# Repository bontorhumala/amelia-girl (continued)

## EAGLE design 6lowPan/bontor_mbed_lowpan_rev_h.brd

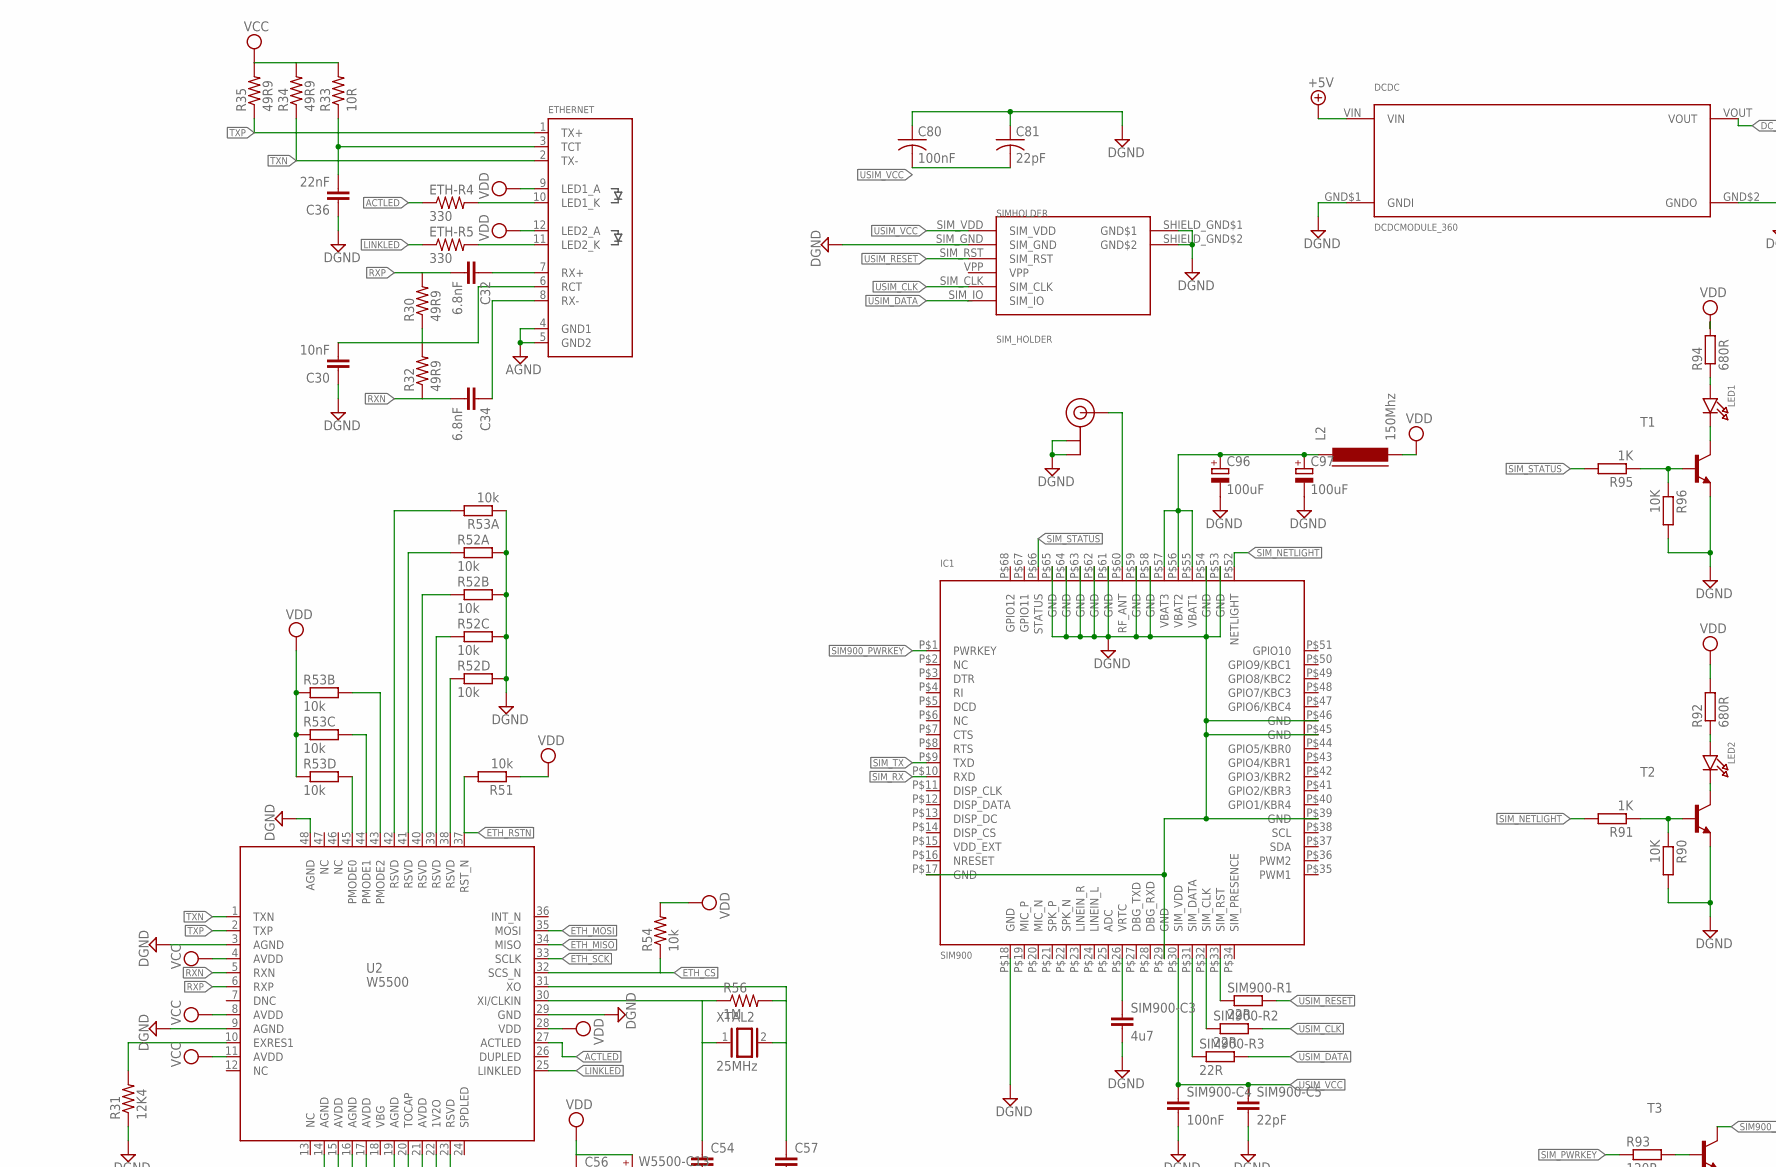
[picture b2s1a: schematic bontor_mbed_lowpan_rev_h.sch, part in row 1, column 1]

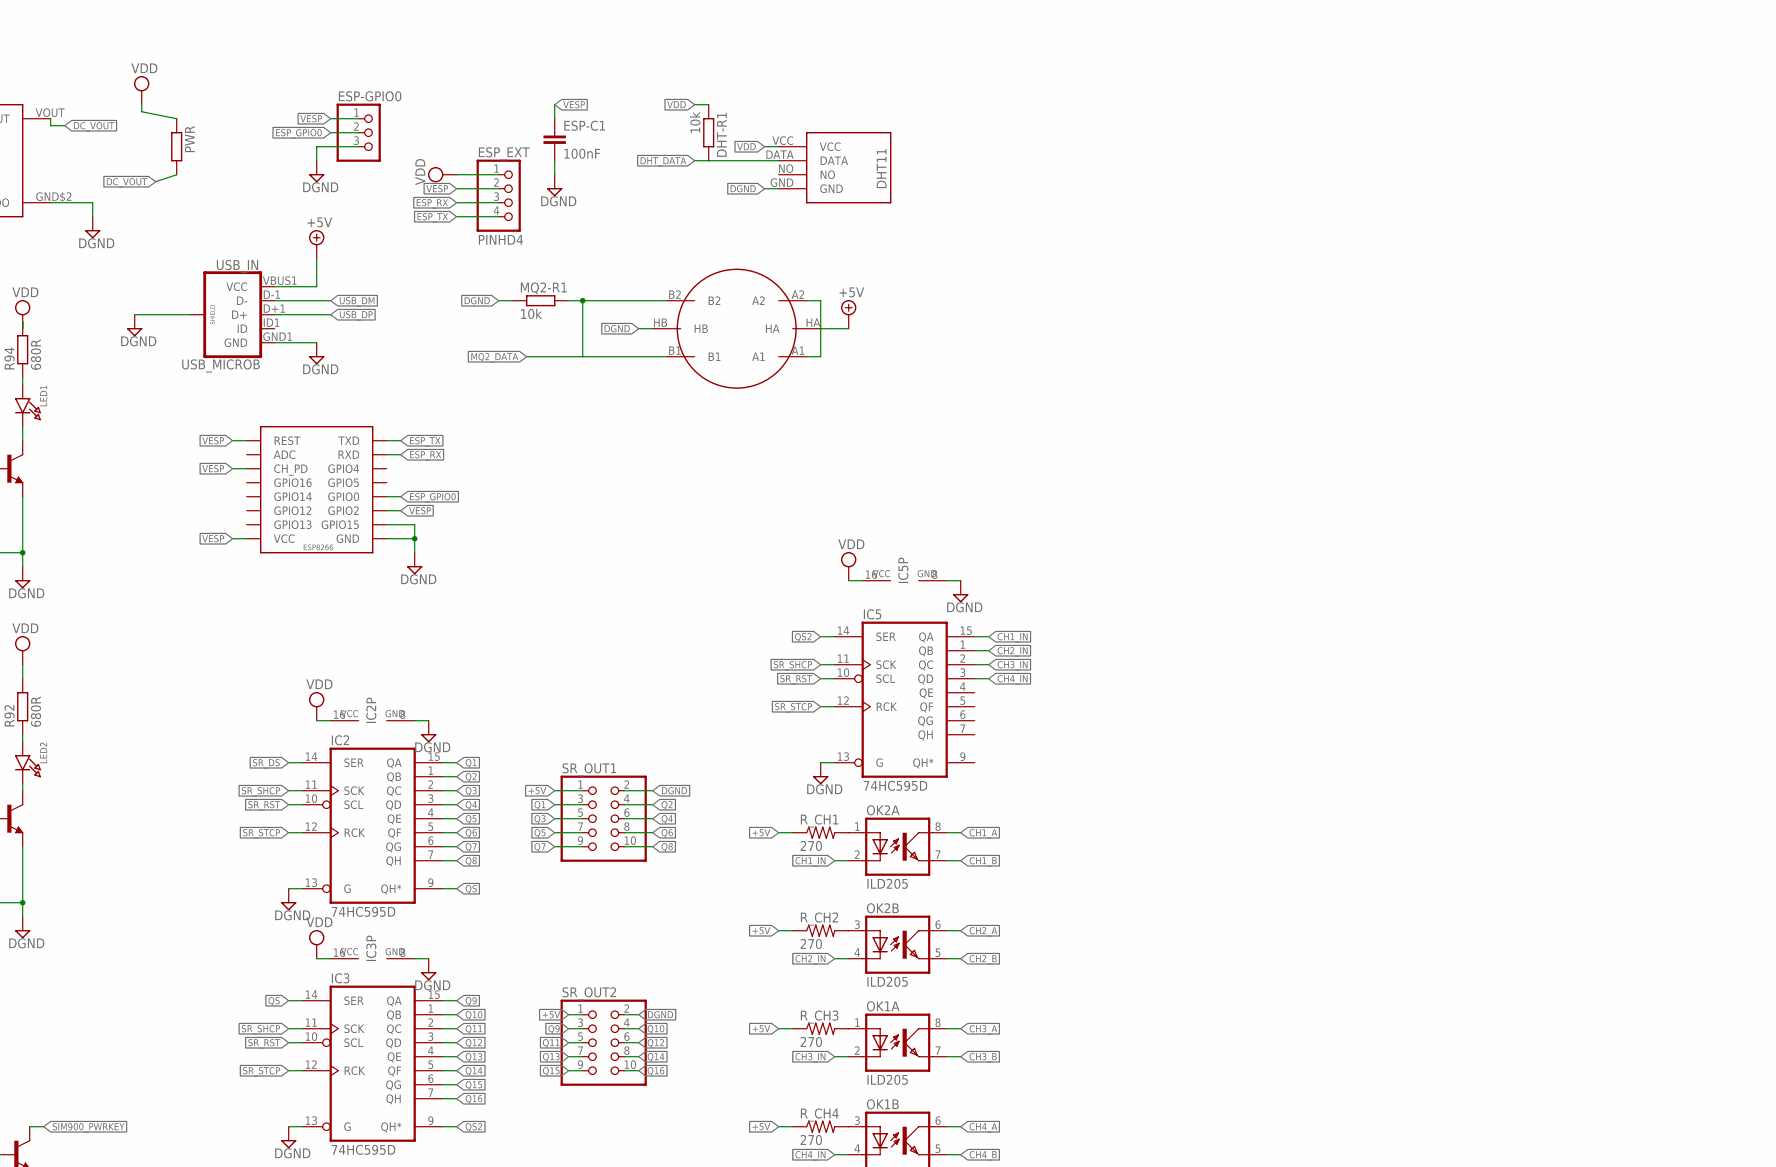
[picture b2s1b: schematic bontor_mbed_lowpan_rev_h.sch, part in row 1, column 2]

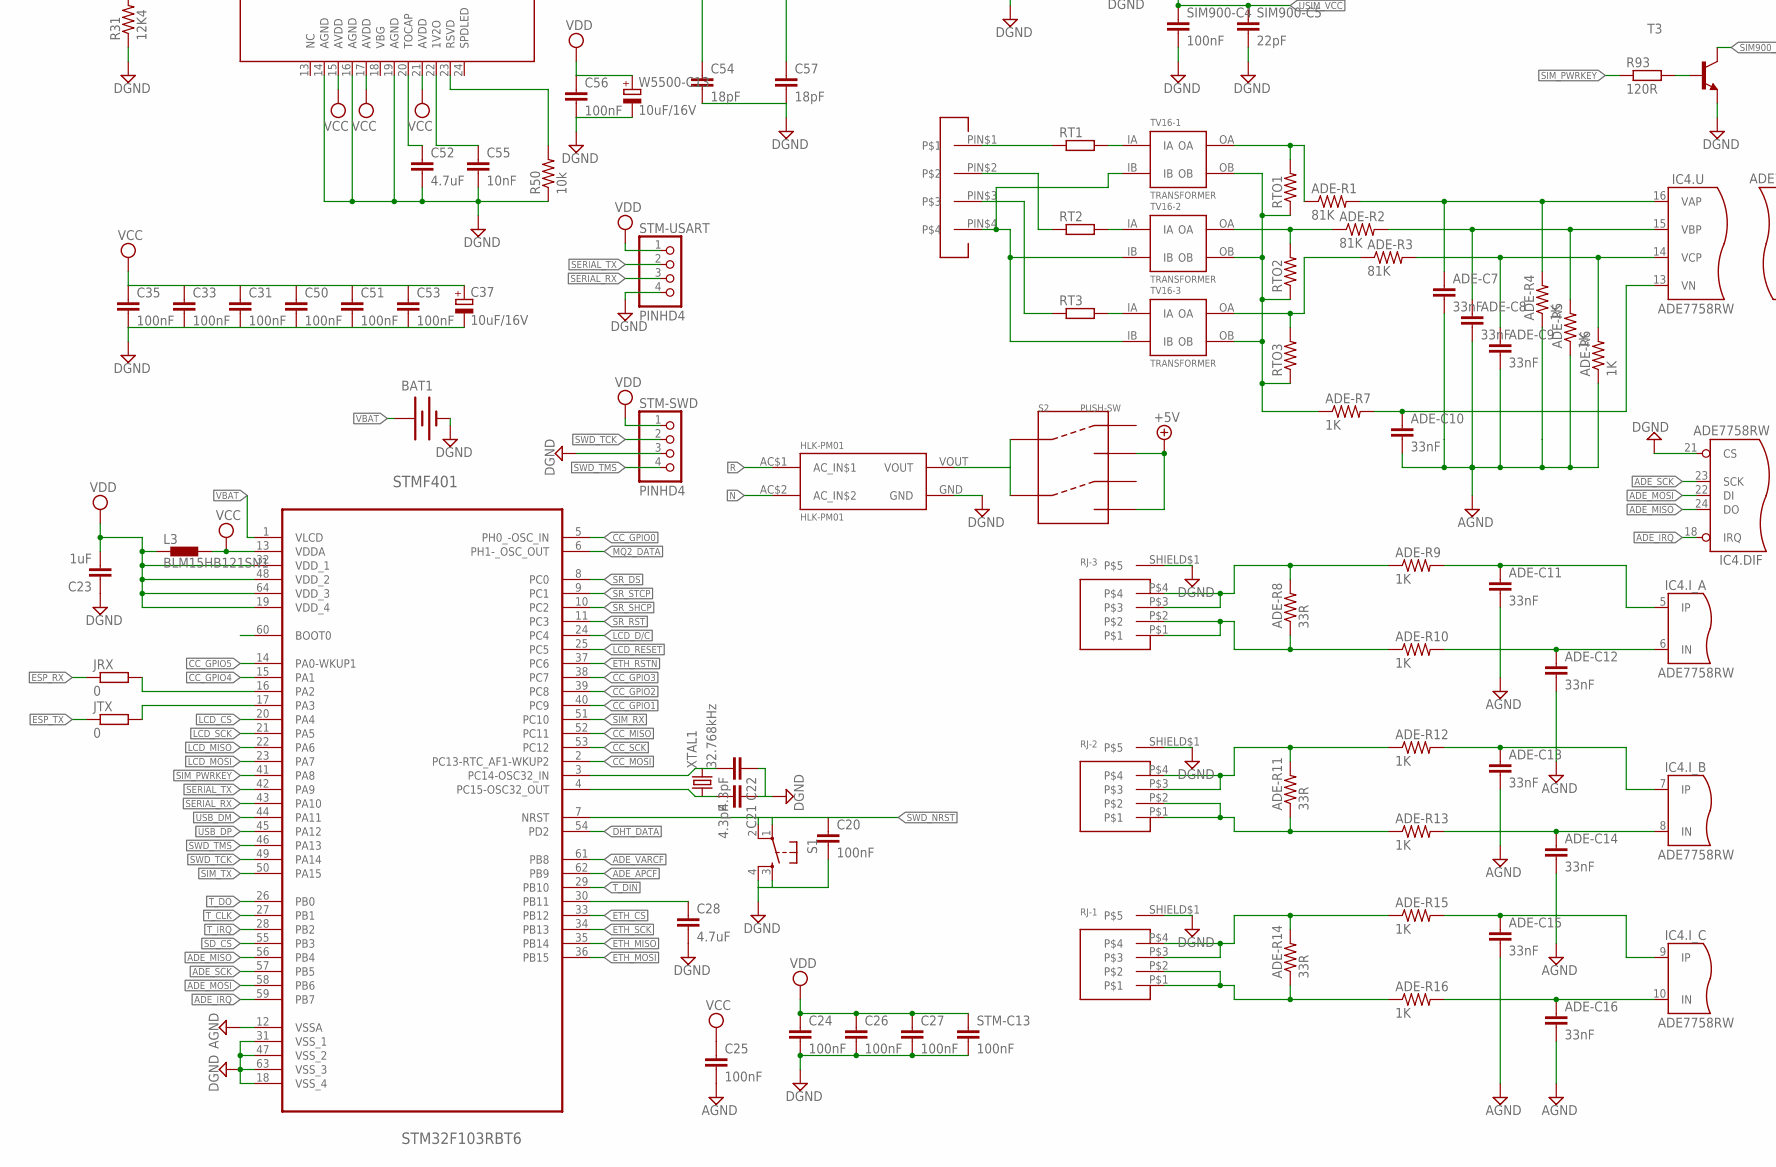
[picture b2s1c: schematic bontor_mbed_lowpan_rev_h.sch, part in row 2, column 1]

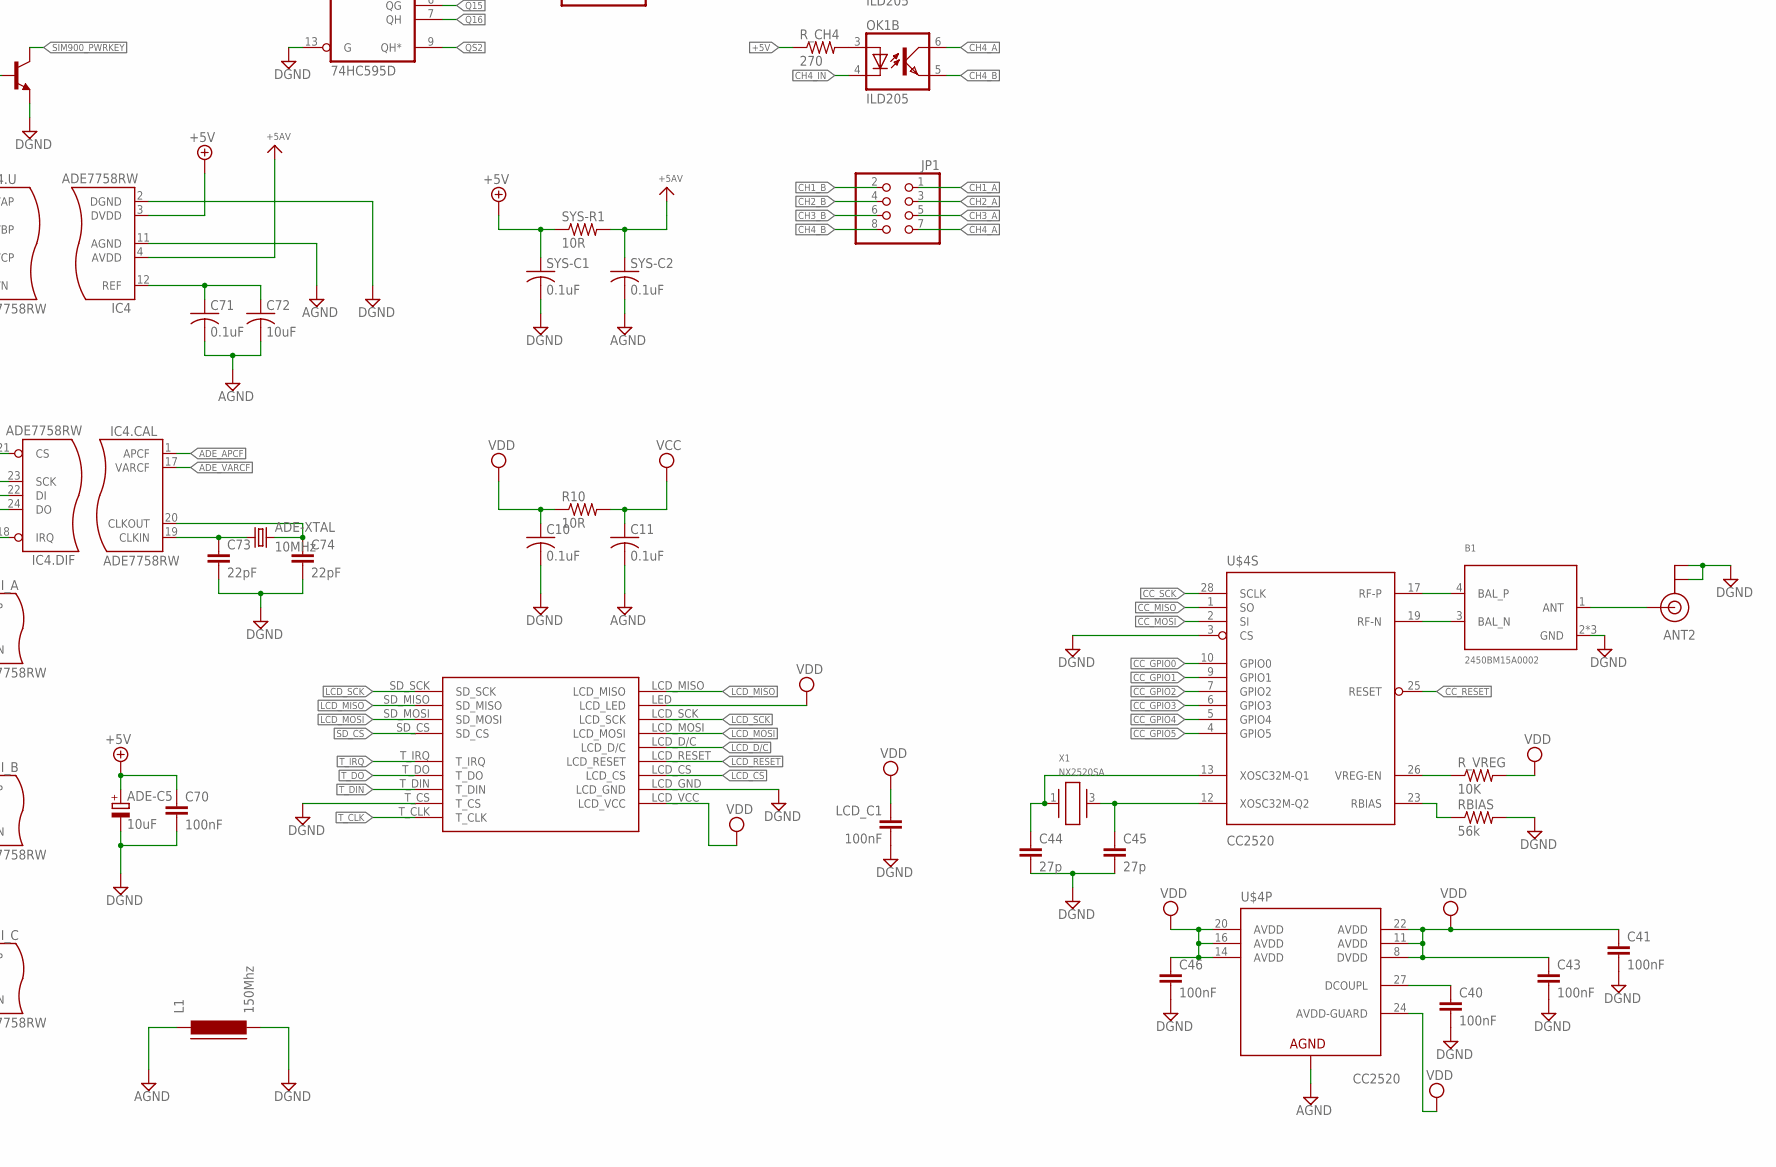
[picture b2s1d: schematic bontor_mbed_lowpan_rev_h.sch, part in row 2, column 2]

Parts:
ADE-C5: 10uF; 153CLV-0605
ADE-C7, ADE-C8, ADE-C9, ADE-C10: 33nF; 0603-CAP
ADE-C11, ADE-C12, ADE-C13, ADE-C14, ADE-C15, ADE-C16: 33nF; 0402-CAP
ADE-R1, ADE-R2, ADE-R3: 81K; 0603-RES
ADE-R4, ADE-R5, ADE-R6, ADE-R7: 1K; 0603-RES
ADE-R8, ADE-R11, ADE-R14: 33R; 0402-RES
ADE-R9, ADE-R10, ADE-R12, ADE-R13, ADE-R15, ADE-R16: 1K; 0402-RES
ADE-XTAL: 10MHz; HC49US
ANT1, ANT2: U.FL
B1: 2450BM15A0002; 2450BM
BAT1: BATTERY12MM; BATTCON_12MM
C10, C11, C71: 0.1uF; C0603
C20, C24, C25, C26, C31, C33, C35, C50, C51, C53, C56, C70: 100nF; C0603
C21, C22: 4.3pF; C0603
C23: 1uF; C0603
C27, C40, C41, C43, C46: 100nF; C0402
C28, C52: 4.7uF; C0603
C30, C55: 10nF; C0603
C32, C34: 6.8nF; C0603
C36: 22nF; C0603
C37: 10uF/16V; 153CLV-0605
C44, C45: 27p; C0201
C54, C57: 18pF; C0603
C72: 10uF; C0805K
C73, C74: 22pF; C0603
C80: 100nF; C0603K
C81: 22pF; C0603K
C96, C97: 100uF; 153CLV-0605
DCDC: DCDCMODULE_360; DCDCMODULE-360
DHT-R1: 10k; R0603
ESP: ESP; WI12
ESP-C1: 100nF; C0603
ESP-GPIO0: PINHD-1X3; 1X03
ESP_EXT: PINHD4
ETH-R4, ETH-R5: 330; R0603
ETHERNET: RJ45J0026D21BNL; RJ45_PULSEJACK
HLK-PM01: HLK-PM01
IC1: SIM900; SIM900_SMT
IC2, IC3, IC5: 74HC595D; SO16
IC4: ADE7758RW; SOIC24
JP1: PINHD-2X4; 2X04
JRX: 0; R0603
JTX: 0; R0603
L1, L2: 150Mhz; FB805
L3: BLM15HB121SN1; 0402
LCD14: LCD_2.4; LCD_TOUCH_2-4
LCD_C1: 100nF; C0603
LED1, LED2: LED0805_NOOUTLINE; CHIPLED_0805_NOOUTLINE
MQ2-R1: 10k; R0603
OK1, OK2: ILD205; SOIC08
PWR: R-EU_R0805; R0805
R10: 10R; 0603-RES
R30, R32, R34, R35: 49R9; R0603
R31: 12K4; R0805
R33: 10R; R0603
R50, R51, R54: 10k; R0603
R52, R53: 10k; RN8P-4R-CRA06S
R56: 1M; R0603
R90, R96: 10K; R0603
R91, R95: 1K; R0603
R92, R94: 680R; R0603
R93: 120R; R0603
RBIAS: 56k; 0402-RES
RJ-1, RJ-2, RJ-3: RJ11-4P-V
RT1, RT2, RT3: R-EU_0309/V; 0309V
RTO1, RTO2, RTO3: R-US_0309_12; 0309_12
R_CH1, R_CH2, R_CH3, R_CH4: 270; 0603-RES
R_VREG: 10K; 0402-RES
S1: TAC_SWITCHPTH; TACTILE-PTH
S2: PUSH-SW; SWITCH-6PIN-LOCK-2.54MM
SENSOR-MQ2: METHANE_SENSOR; MQ-3
SIM900-C3: 4u7; C0603
SIM900-C4: 100nF; C0603
SIM900-C5: 22pF; C0603
SIM900-R1, SIM900-R2, SIM900-R3: 22R; R0603
SIMHOLDER: SIM_HOLDER; SIMHOLDER-PUSHPUSH
SR_OUT1, SR_OUT2: PINHD-2X5; 2X05
STM-C13: 100nF; C0603
STM-SWD: PINHD4
STM-USART: PINHD4
STMF401: STM32F103RBT6; QFP50P1200X1200X160-64N
SYS-C1, SYS-C2: 0.1uF; C0603
SYS-R1: 10R; 0603-RES
T1, T2, T3: MMBT2222ALT1-NPN-SOT23-BEC; SOT23-BEC
TERM_BLOCK: TERMINAL_BLOCK_TW; TERMINAL-TWO-WAY
TV16-1, TV16-2, TV16-3: TRANSFORMER; TV16
U2: W5500
U$4: CC2520; QFN50P500X500X100-29N
U$17: DHT11
USB_IN: USB_MICROB; USB-B-MICRO-SMD_V03
W5500-C13: 10uF/16V; 153CLV-0605
X1: NX2520SA
XTAL1: 32.768kHz; TC26H
XTAL2: 25MHz; QS

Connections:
+5V: ADE-C5.+, C70.1, DCDC.VIN, IC4.3 (DVDD), R_CH1.1, R_CH2.1, R_CH3.1, R_CH4.1, S2.P$3, S2.P$6, SENSOR-MQ2.A1, SENSOR-MQ2.A2, SENSOR-MQ2.HA, SR_OUT1.1, SR_OUT2.1, SYS-C1.1, SYS-R1.1, USB_IN.VBUS1 (VCC)
ACTLED: ETH-R4.1, U2.27 (ACTLED)
ADE_APCF: IC4.1 (APCF), STMF401.62 (PB9)
ADE_IRQ: IC4.18 (IRQ), STMF401.59 (PB7)
ADE_MISO: IC4.24 (DO), STMF401.56 (PB4)
ADE_MOSI: IC4.22 (DI), STMF401.58 (PB6)
ADE_SCK: IC4.23 (SCK), STMF401.57 (PB5)
ADE_VARCF: IC4.17 (VARCF), STMF401.61 (PB8)
AGND: ADE-C7.2, ADE-C8.2, ADE-C9.2, ADE-C10.2, ADE-C11.2, ADE-C12.2, ADE-C13.2, ADE-C14.2, ADE-C15.2, ADE-C16.2, ADE-R4.1, ADE-R5.1, ADE-R6.1, C11.2, C25.2, C71.2, C72.2, ETHERNET.4 (GND1), ETHERNET.5 (GND2), IC4.11 (AGND), L1.1, STMF401.12 (VSSA), SYS-C2.2, U$4.29 (AGND)
AVDD: IC4.4 (AVDD), SYS-C2.1, SYS-R1.2
CC_GPIO0: STMF401.5 (PH0_-OSC_IN), U$4.10 (GPIO0)
CC_GPIO1: STMF401.40 (PC9), U$4.9 (GPIO1)
CC_GPIO2: STMF401.39 (PC8), U$4.7 (GPIO2)
CC_GPIO3: STMF401.38 (PC7), U$4.6 (GPIO3)
CC_GPIO4: STMF401.15 (PA1), U$4.5 (GPIO4)
CC_GPIO5: STMF401.14 (PA0-WKUP1), U$4.4 (GPIO5)
CC_MISO: STMF401.52 (PC11), U$4.1 (SO)
CC_MOSI: STMF401.2 (PC13-RTC_AF1-WKUP2), U$4.2 (SI)
CC_RESET: U$4.25 (RESET)
CC_SCK: STMF401.53 (PC12), U$4.28 (SCLK)
CH1_A: JP1.1, OK2.8 (COL)
CH1_B: JP1.2, OK2.7 (EMIT)
CH1_IN: IC5.15 (QA), OK2.2 (C)
CH2_A: JP1.3, OK2.6 (COL)
CH2_B: JP1.4, OK2.5 (EMIT)
CH2_IN: IC5.1 (QB), OK2.4 (C)
CH3_A: JP1.5, OK1.8 (COL)
CH3_B: JP1.6, OK1.7 (EMIT)
CH3_IN: IC5.2 (QC), OK1.2 (C)
CH4_A: JP1.7, OK1.6 (COL)
CH4_B: JP1.8, OK1.5 (EMIT)
CH4_IN: IC5.3 (QD), OK1.4 (C)
DC_VOUT: DCDC.VOUT, PWR.2
DGND: ADE-C5.-, ANT1.P$1 (GND), ANT1.P$2 (GND), ANT2.P$1 (GND), ANT2.P$2 (GND), B1.2 (GND), B1.5 (GND), B1.6 (GND), BAT1.GND (-), C10.2, C20.2, C21.1, C22.1, C23.1, C24.2, C26.2, C27.2, C28.2, C30.1, C31.2, C33.2, C35.2, C36.1, C37.-, C40.2, C41.2, C43.2, C44.2, C45.2, C46.2, C50.2, C51.2, C52.2, C53.2, C54.2, C55.2, C56.2, C57.2, C70.2, C73.2, C74.2, C80.1, C81.1, C96.-, C97.-, DCDC.GND$1 (GNDI), DCDC.GND$2 (GNDO), ESP.GND, ESP.GPIO15, ESP-C1.2, ESP-GPIO0.3, HLK-PM01.GND, IC1.P$17 (GND), IC1.P$18 (GND), IC1.P$29 (GND), IC1.P$39 (GND), IC1.P$45 (GND), IC1.P$46 (GND), IC1.P$53 (GND), IC1.P$54 (GND), IC1.P$58 (GND), IC1.P$59 (GND), IC1.P$61 (GND), IC1.P$62 (GND), IC1.P$63 (GND), IC1.P$64 (GND), IC1.P$65 (GND), IC2.8 (GND), IC2.13 (G), IC3.8 (GND), IC3.13 (G), IC4.2 (DGND), IC4.21 (CS), IC5.8 (GND), IC5.13 (G), L1.2, LCD14.LCD_GND, LCD14.T_CS, LCD_C1.2, MQ2-R1.1, R31.1, R50.1, R52.5 (2), R52.6 (2), R52.7 (2), R52.8 (2), R53.1, R90.2, R96.2, RBIAS.2, RJ-1.SHIELD$1, RJ-2.SHIELD$1, RJ-3.SHIELD$1, S1.3, S1.4, SENSOR-MQ2.HB, SIM900-C3.2, SIM900-C4.2, SIM900-C5.2, SIMHOLDER.SHIELD_GND$1 (GND$1), SIMHOLDER.SHIELD_GND$2 (GND$2), SIMHOLDER.SIM_GND, SR_OUT1.2, SR_OUT2.2, STM-C13.2, STM-SWD.3, STM-USART.4, STMF401.18 (VSS_4), STMF401.31 (VSS_1), STMF401.47 (VSS_2), STMF401.63 (VSS_3), SYS-C1.2, T1.E, T2.E, T3.E, U2.3 (AGND), U2.9 (AGND), U2.14 (AGND), U2.16 (AGND), U2.19 (AGND), U2.29 (GND), U2.48 (AGND), U$4.3 (CS), U$17.GND, USB_IN.GND1 (GND), USB_IN.SHIELD1 (SHIELD), USB_IN.SHIELD2 (SHIELD), USB_IN.SHIELD3 (SHIELD), W5500-C13.-
DHT_DATA: DHT-R1.2, STMF401.54 (PD2), U$17.DATA
ESP_GPIO0: ESP.GPIO00 (GPIO0), ESP-GPIO0.2
ESP_RX: ESP.RXD, ESP_EXT.3, JRX.1
ESP_TX: ESP.TXD, ESP_EXT.4, JTX.1
ETH_CS: R54.1, STMF401.33 (PB12), U2.32 (SCS_N)
ETH_MISO: STMF401.35 (PB14), U2.34 (MISO)
ETH_MOSI: STMF401.36 (PB15), U2.35 (MOSI)
ETH_RSTN: R51.2, STMF401.37 (PC6), U2.37 (RST_N)
ETH_SCK: STMF401.34 (PB13), U2.33 (SCLK)
GPIO11: IC1.P$67 (GPIO11)
GPIO12: IC1.P$68 (GPIO12)
IBN: ADE-R11.1, ADE-R13.1, RJ-2.P$1, RJ-2.P$2
ICN: ADE-R14.1, ADE-R16.1, RJ-1.P$1, RJ-1.P$2
LCD_CS: LCD14.LCD_CS, STMF401.20 (PA4)
LCD_D/C: LCD14.LCD_D/C, STMF401.24 (PC4)
LCD_MISO: LCD14.LCD_MISO, LCD14.SD_MISO, STMF401.22 (PA6)
LCD_MOSI: LCD14.LCD_MOSI, LCD14.SD_MOSI, STMF401.23 (PA7)
LCD_RESET: LCD14.LCD_RESET, STMF401.25 (PC5)
LCD_SCK: LCD14.LCD_SCK, LCD14.SD_SCK, STMF401.21 (PA5)
LINKLED: ETH-R5.1, U2.25 (LINKLED)
MQ2_DATA: MQ2-R1.2, SENSOR-MQ2.B1, SENSOR-MQ2.B2, STMF401.6 (PH1-_OSC_OUT)
N: HLK-PM01.AC$2 (AC_IN$2), TERM_BLOCK.PIN$4, TV16-1.IB, TV16-2.IB, TV16-3.IB
unnamed: C22.2, STMF401.3 (PC14-OSC32_IN), XTAL1.2
unnamed: C21.2, STMF401.4 (PC15-OSC32_OUT), XTAL1.1
unnamed: IC1.P$31 (SIM_DATA), SIM900-R3.1
unnamed: OK2.1 (A), R_CH1.2
unnamed: OK2.3 (A), R_CH2.2
unnamed: OK1.1 (A), R_CH3.2
unnamed: IC1.P$32 (SIM_CLK), SIM900-R2.1
unnamed: R_VREG.1, U$4.26 (VREG-EN)
unnamed: ADE-C9.1, ADE-R3.2, ADE-R6.2, IC4.14 (VCP)
unnamed: ETH-R4.2, ETHERNET.10 (LED1_K)
unnamed: ETH-R5.2, ETHERNET.11 (LED2_K)
unnamed: IC1.P$33 (SIM_RST), SIM900-R1.1
unnamed: IC1.P$26 (VRTC), SIM900-C3.1
unnamed: ANT1.P$3 (SIGNAL), IC1.P$60 (RF_ANT)
unnamed: LED1.A, R94.1
unnamed: LED1.C, T1.C
unnamed: R95.1, R96.1, T1.B
unnamed: LED2.A, R92.1
unnamed: LED2.C, T2.C
unnamed: R90.1, R91.1, T2.B
unnamed: C32.1, ETHERNET.7 (RX+)
unnamed: C36.2, ETHERNET.3 (TCT), R33.1
unnamed: ADE-C15.1, ADE-R15.2, IC4.9 (IP)
unnamed: ADE-R11.2, ADE-R12.1, RJ-2.P$3, RJ-2.P$4
unnamed: C34.1, ETHERNET.8 (RX-)
unnamed: ADE-C11.1, ADE-R9.2, IC4.5 (IP)
unnamed: ADE-C12.1, ADE-R10.2, IC4.6 (IN)
unnamed: C30.2, ETHERNET.6 (RCT), R30.1, R32.2
unnamed: ADE-C14.1, ADE-R13.2, IC4.8 (IN)
unnamed: ADE-C13.1, ADE-R12.2, IC4.7 (IP)
unnamed: C71.1, C72.1, IC4.12 (REF)
unnamed: ADE-XTAL.1, C73.1, IC4.19 (CLKIN)
unnamed: ADE-XTAL.2, C74.1, IC4.20 (CLKOUT)
unnamed: ADE-C10.1, ADE-R7.2, IC4.13 (VN)
unnamed: ADE-R2.1, RTO2.2, TV16-2.OA
unnamed: ADE-C8.1, ADE-R2.2, ADE-R5.2, IC4.15 (VBP)
unnamed: C52.1, U2.20 (TOCAP)
unnamed: ADE-R8.2, ADE-R9.1, RJ-3.P$3, RJ-3.P$4
unnamed: ADE-C16.1, ADE-R16.2, IC4.10 (IN)
unnamed: C55.1, U2.22 (1V2O)
unnamed: R50.2, U2.23 (RSVD)
unnamed: C40.1, U$4.27 (DCOUPL)
unnamed: R93.2, T3.B
unnamed: OK1.3 (A), R_CH4.2
unnamed: ADE-R8.1, ADE-R10.1, RJ-3.P$1, RJ-3.P$2
unnamed: ADE-R14.2, ADE-R15.1, RJ-1.P$3, RJ-1.P$4
unnamed: C57.1, R56.2, U2.31 (XO), XTAL2.2
unnamed: R31.2, U2.10 (EXRES1)
unnamed: ADE-C7.1, ADE-R1.2, ADE-R4.2, IC4.16 (VAP)
unnamed: ADE-R1.1, RTO1.2, TV16-1.OA
unnamed: ADE-R7.1, RTO1.1, RTO2.1, RTO3.1, TV16-1.OB, TV16-2.OB, TV16-3.OB
unnamed: R52.4 (1), U2.38 (RSVD)
unnamed: R52.3 (1), U2.39 (RSVD)
unnamed: R52.2 (1), U2.40 (RSVD)
unnamed: R52.1, U2.41 (RSVD)
unnamed: R53.8 (2), U2.42 (RSVD)
unnamed: R53.7 (2), U2.43 (PMODE2)
unnamed: R53.6 (2), U2.44 (PMODE1)
unnamed: R53.5 (2), U2.45 (PMODE0)
unnamed: ADE-R3.1, RTO3.2, TV16-3.OA
unnamed: C54.1, R56.1, U2.30 (XI/CLKIN), XTAL2.1
unnamed: C96.+, C97.+, IC1.P$55 (VBAT1), IC1.P$56 (VBAT2), IC1.P$57 (VBAT3), L2.1
unnamed: C44.1, U$4.13 (XOSC32M-Q1), X1.1
unnamed: C45.1, U$4.12 (XOSC32M-Q2), X1.3 (2)
unnamed: JRX.2, STMF401.16 (PA2)
unnamed: JTX.2, STMF401.17 (PA3)
unnamed: RT3.2, TV16-3.IA
unnamed: RT2.2, TV16-2.IA
unnamed: RT1.2, TV16-1.IA
unnamed: RBIAS.1, U$4.23 (RBIAS)
unnamed: C28.1, STMF401.30 (PB11)
unnamed: B1.4 (BAL_P), U$4.17 (RF-P)
unnamed: HLK-PM01.VOUT, S2.P$1, S2.P$4
unnamed: B1.3 (BAL_N), U$4.19 (RF-N)
unnamed: ANT2.P$3 (SIGNAL), B1.1 (ANT)
Q1: IC2.15 (QA), SR_OUT1.3
Q2: IC2.1 (QB), SR_OUT1.4
Q3: IC2.2 (QC), SR_OUT1.5
Q4: IC2.3 (QD), SR_OUT1.6
Q5: IC2.4 (QE), SR_OUT1.7
Q6: IC2.5 (QF), SR_OUT1.8
Q7: IC2.6 (QG), SR_OUT1.9
Q8: IC2.7 (QH), SR_OUT1.10
Q9: IC3.15 (QA), SR_OUT2.3
Q10: IC3.1 (QB), SR_OUT2.4
Q11: IC3.2 (QC), SR_OUT2.5
Q12: IC3.3 (QD), SR_OUT2.6
Q13: IC3.4 (QE), SR_OUT2.7
Q14: IC3.5 (QF), SR_OUT2.8
Q15: IC3.6 (QG), SR_OUT2.9
Q16: IC3.7 (QH), SR_OUT2.10
QS: IC2.9 (QH*), IC3.14 (SER)
QS2: IC3.9 (QH*), IC5.14 (SER)
R: HLK-PM01.AC$1 (AC_IN$1), RT1.1, TERM_BLOCK.PIN$1
RXN: C34.2, R32.1, U2.5 (RXN)
RXP: C32.2, R30.2, U2.6 (RXP)
S: RT2.1, TERM_BLOCK.PIN$2
SD_CS: LCD14.SD_CS, STMF401.55 (PB3)
SERIAL_RX: STM-USART.3, STMF401.43 (PA10)
SERIAL_TX: STM-USART.2, STMF401.42 (PA9)
SIM900_PWRKEY: IC1.P$1 (PWRKEY), T3.C
SIM_NETLIGHT: IC1.P$52 (NETLIGHT), R91.2
SIM_PWRKEY: R93.1, STMF401.41 (PA8)
SIM_RX: IC1.P$10 (RXD), STMF401.51 (PC10)
SIM_STATUS: IC1.P$66 (STATUS), R95.2
SIM_TX: IC1.P$9 (TXD), STMF401.50 (PA15)
SR_DS: IC2.14 (SER), STMF401.8 (PC0)
SR_RST: IC2.10 (SCL), IC3.10 (SCL), IC5.10 (SCL), STMF401.11 (PC3)
SR_SHCP: IC2.11 (SCK), IC3.11 (SCK), IC5.11 (SCK), STMF401.10 (PC2)
SR_STCP: IC2.12 (RCK), IC3.12 (RCK), IC5.12 (RCK), STMF401.9 (PC1)
SWD_NRST: C20.1, S1.1, S1.2, STMF401.7 (NRST)
SWD_TCK: STM-SWD.2, STMF401.49 (PA14)
SWD_TMS: STM-SWD.4, STMF401.46 (PA13)
T: RT3.1, TERM_BLOCK.PIN$3
TXN: ETHERNET.2 (TX-), R34.1, U2.1 (TXN)
TXP: ETHERNET.1 (TX+), R35.1, U2.2 (TXP)
T_CLK: LCD14.T_CLK, STMF401.27 (PB1)
T_DIN: LCD14.T_DIN, STMF401.29 (PB10)
T_DO: LCD14.T_DO, STMF401.26 (PB0)
T_IRQ: LCD14.T_IRQ, STMF401.28 (PB2)
USB_DM: STMF401.44 (PA11), USB_IN.D-1 (D-)
USB_DP: STMF401.45 (PA12), USB_IN.D+1 (D+)
USIM_CLK: SIM900-R2.2, SIMHOLDER.SIM_CLK
USIM_DATA: SIM900-R3.2, SIMHOLDER.SIM_IO
USIM_RESET: SIM900-R1.2, SIMHOLDER.SIM_RST
USIM_VCC: C80.2, C81.2, IC1.P$30 (SIM_VDD), SIM900-C4.1, SIM900-C5.1, SIMHOLDER.SIM_VDD
VBAT: BAT1.PWR@1 (+), STMF401.1 (VLCD)
VCC: C11.1, C25.1, C31.1, C33.1, C35.1, C37.+, C50.1, C51.1, C53.1, L3.2, R10.2, R33.2, R34.2, R35.2, STMF401.13 (VDDA), U2.4 (AVDD), U2.8 (AVDD), U2.11 (AVDD), U2.15 (AVDD), U2.17 (AVDD), U2.21 (AVDD)
VDD: C10.1, C23.2, C24.1, C26.1, C27.1, C41.1, C43.1, C46.1, C56.1, DHT-R1.1, ESP_EXT.1, ETHERNET.9 (LED1_A), ETHERNET.12 (LED2_A), IC2.16 (VCC), IC3.16 (VCC), IC5.16 (VCC), L2.2, L3.1, LCD14.LCD_VCC, LCD14.LED (LCD_LED), LCD_C1.1, PWR.1, R10.1, R51.1, R53.2 (1), R53.3 (1), R53.4 (1), R54.2, R92.2, R94.2, R_VREG.2, STM-C13.1, STM-SWD.1, STM-USART.1, STMF401.19 (VDD_4), STMF401.32 (VDD_1), STMF401.48 (VDD_2), STMF401.64 (VDD_3), U2.28 (VDD), U$4.8 (DVDD), U$4.11 (AVDD), U$4.14 (AVDD), U$4.16 (AVDD), U$4.20 (AVDD), U$4.22 (AVDD), U$4.24 (AVDD-GUARD), U$17.VCC, W5500-C13.+
VESP: ESP.CH_PD, ESP.GPIO02 (GPIO2), ESP.REST, ESP.VCC, ESP-C1.1, ESP-GPIO0.1, ESP_EXT.2

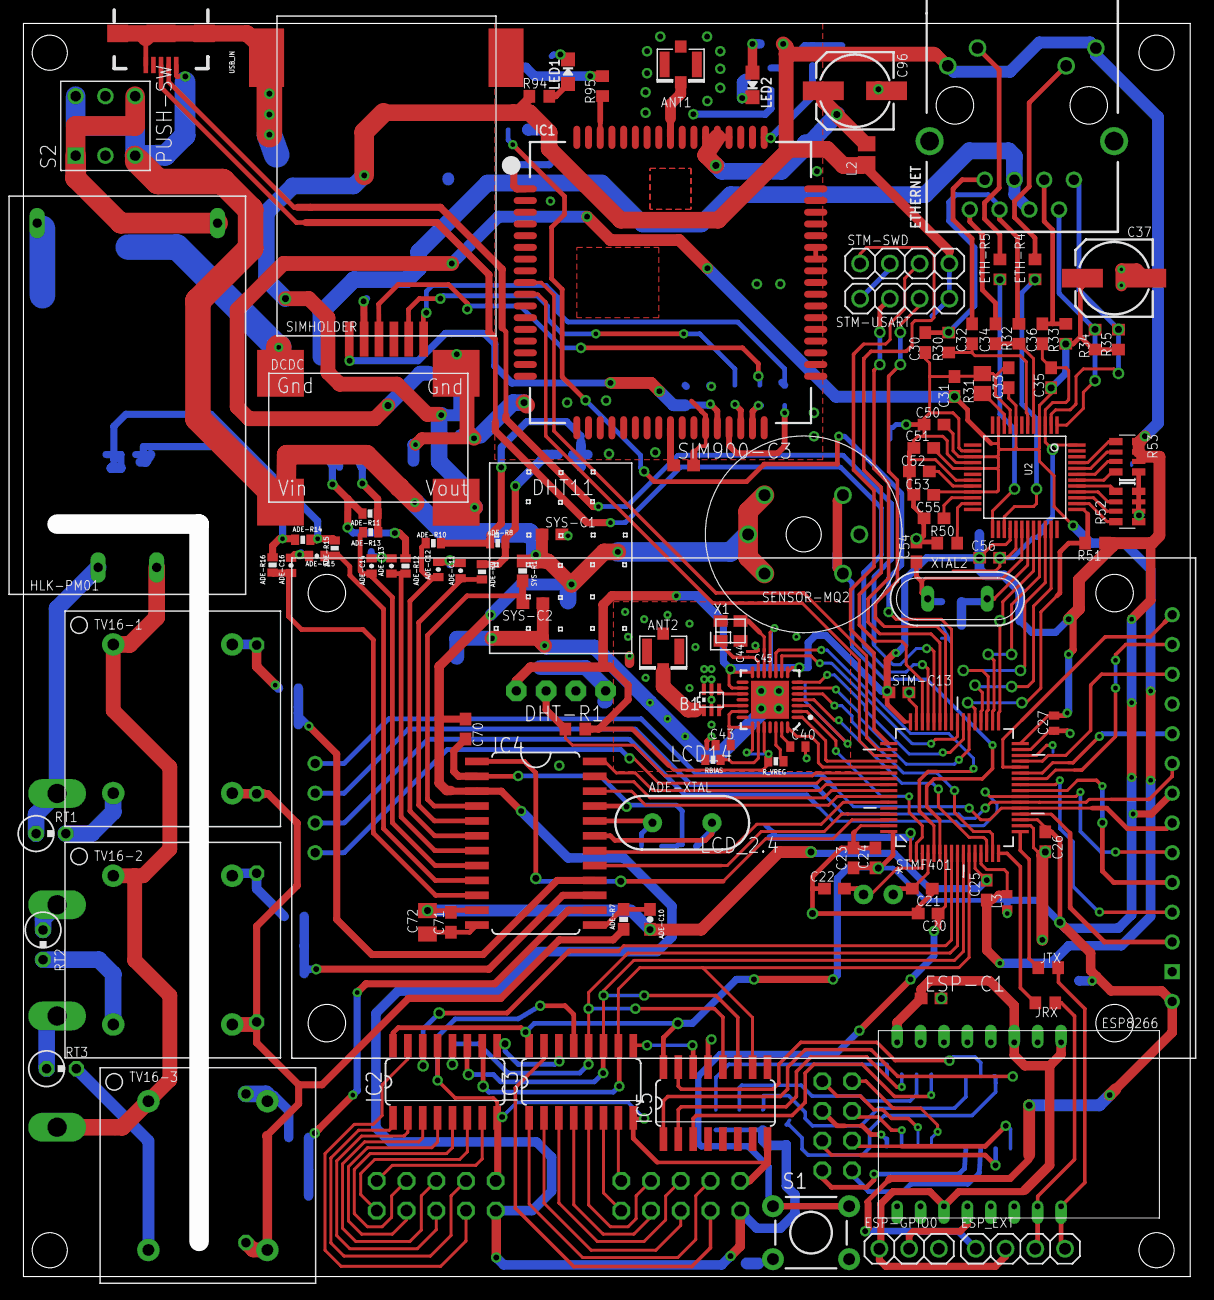
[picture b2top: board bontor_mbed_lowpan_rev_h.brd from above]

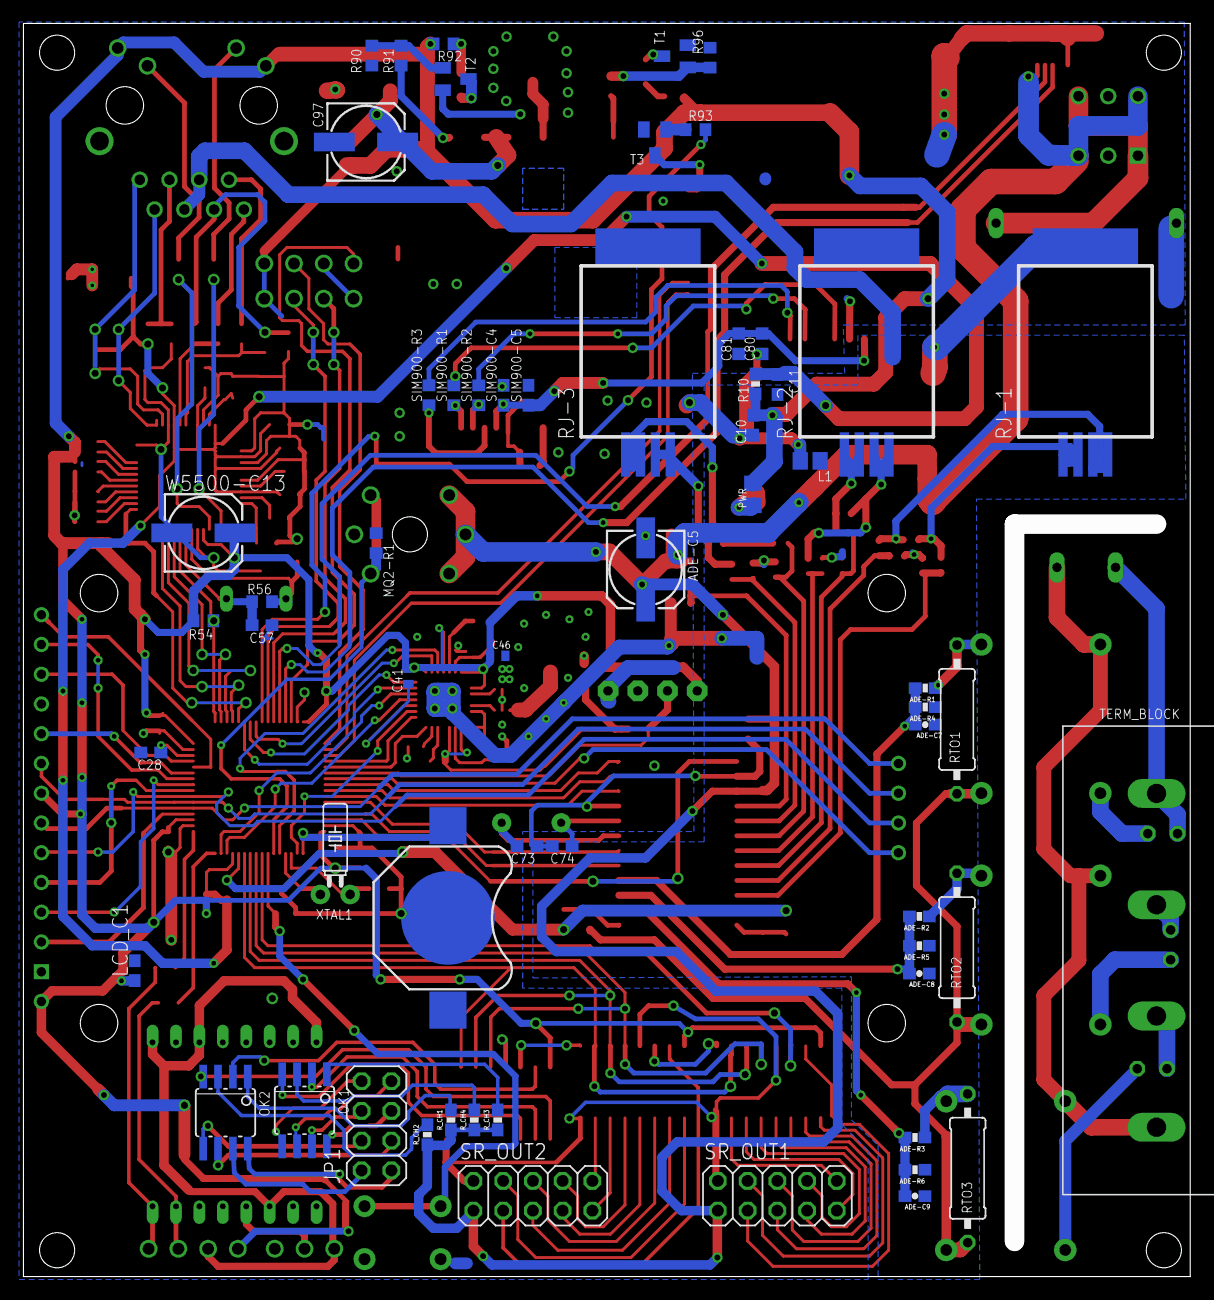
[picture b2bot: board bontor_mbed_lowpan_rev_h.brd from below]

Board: 2 copper layers, 99.6 x 107.0 mm, 172 parts (60 on the bottom side), 183 nets.

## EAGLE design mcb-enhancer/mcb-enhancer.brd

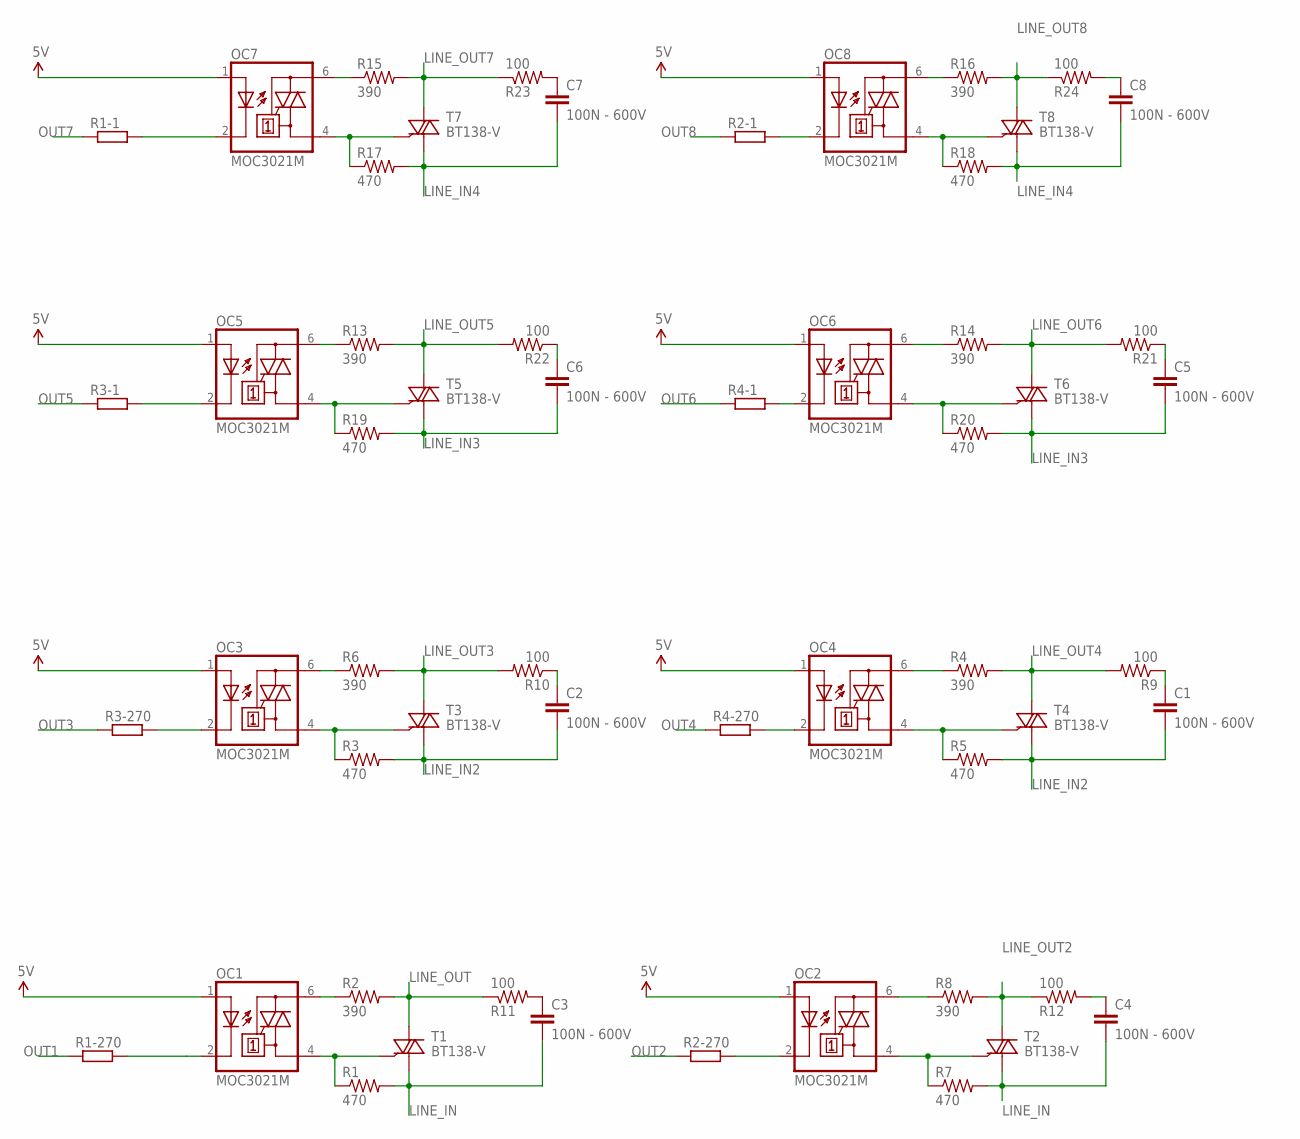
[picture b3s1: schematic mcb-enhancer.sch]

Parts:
C1, C2, C3, C4, C5, C6, C7, C8: 100N - 600V; C050-030X075
OC1, OC2, OC3, OC4, OC5, OC6, OC7, OC8: MOC3021M; DIL06
R1, R3, R5, R7, R17, R18, R19, R20: 470; 0207/7
R1-1, R1-270, R2-1, R2-270, R3-1, R3-270, R4-1, R4-270: R-EU_0309/V; 0309V
R2, R4, R6, R8, R13, R14, R15, R16: 390; 0207/7
R9, R10, R11, R12, R21, R22, R23, R24: 100; 0207/7
T1, T2, T3, T4, T5, T6, T7, T8: BT138-V; TO220BV

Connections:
5V: OC1.1 (A), OC2.1 (A), OC3.1 (A), OC4.1 (A), OC5.1 (A), OC6.1 (A), OC7.1 (A), OC8.1 (A)
LINE_IN: C3.2, C4.2, R1.2, R7.2, T1.T1 (A1), T2.T1 (A1)
LINE_IN2: C1.2, C2.2, R3.2, R5.2, T3.T1 (A1), T4.T1 (A1)
LINE_IN3: C5.2, C6.2, R19.2, R20.2, T5.T1 (A1), T6.T1 (A1)
LINE_IN4: C7.2, C8.2, R17.2, R18.2, T7.T1 (A1), T8.T1 (A1)
LINE_OUT: R2.2, R11.1, T1.T2 (A2)
LINE_OUT2: R8.2, R12.1, T2.T2 (A2)
LINE_OUT3: R6.2, R10.2, T3.T2 (A2)
LINE_OUT4: R4.2, R9.2, T4.T2 (A2)
LINE_OUT5: R13.2, R22.2, T5.T2 (A2)
LINE_OUT6: R14.2, R21.2, T6.T2 (A2)
LINE_OUT7: R15.2, R23.1, T7.T2 (A2)
LINE_OUT8: R16.2, R24.1, T8.T2 (A2)
unnamed: OC1.6 (A2), R2.1
unnamed: OC4.6 (A2), R4.1
unnamed: OC3.4 (A1), R3.1, T3.G
unnamed: OC3.6 (A2), R6.1
unnamed: OC4.4 (A1), R5.1, T4.G
unnamed: C1.1, R9.1
unnamed: C2.1, R10.1
unnamed: C3.1, R11.2
unnamed: OC1.4 (A1), R1.1, T1.G
unnamed: OC2.6 (A2), R8.1
unnamed: OC2.4 (A1), R7.1, T2.G
unnamed: OC5.6 (A2), R13.1
unnamed: OC2.2 (C), R2-270.2
unnamed: OC3.2 (C), R3-270.2
unnamed: OC4.2 (C), R4-270.2
unnamed: C4.1, R12.2
unnamed: OC7.2 (C), R1-1.2
unnamed: OC8.2 (C), R2-1.2
unnamed: OC5.2 (C), R3-1.2
unnamed: OC6.2 (C), R4-1.2
unnamed: OC7.4 (A1), R17.1, T7.G
unnamed: OC8.6 (A2), R16.1
unnamed: OC8.4 (A1), R18.1, T8.G
unnamed: OC7.6 (A2), R15.1
unnamed: OC6.6 (A2), R14.1
unnamed: OC5.4 (A1), R19.1, T5.G
unnamed: OC6.4 (A1), R20.1, T6.G
unnamed: C5.1, R21.1
unnamed: C6.1, R22.1
unnamed: C7.1, R23.2
unnamed: C8.1, R24.2
OUT1: R1-270.1
OUT2: R2-270.1
OUT3: R3-270.1
OUT4: R4-270.1
OUT5: R3-1.1
OUT6: R4-1.1
OUT7: R1-1.1
OUT8: R2-1.1

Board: 2 copper layers, 56 parts (0 on the bottom side), 44 nets, no tracks yet.
